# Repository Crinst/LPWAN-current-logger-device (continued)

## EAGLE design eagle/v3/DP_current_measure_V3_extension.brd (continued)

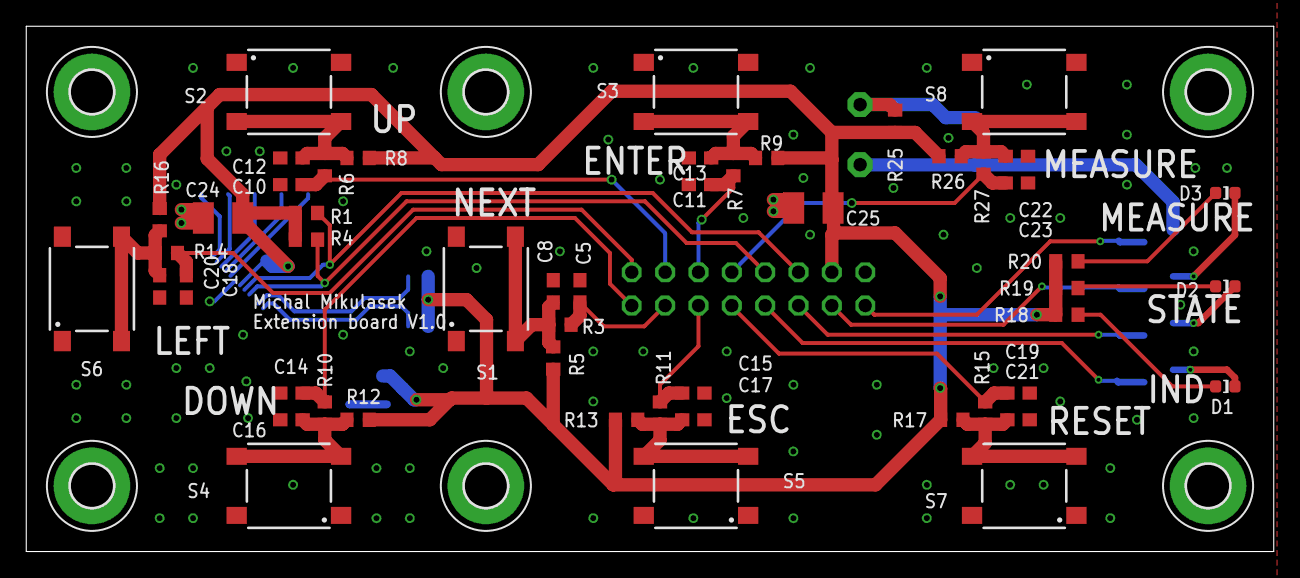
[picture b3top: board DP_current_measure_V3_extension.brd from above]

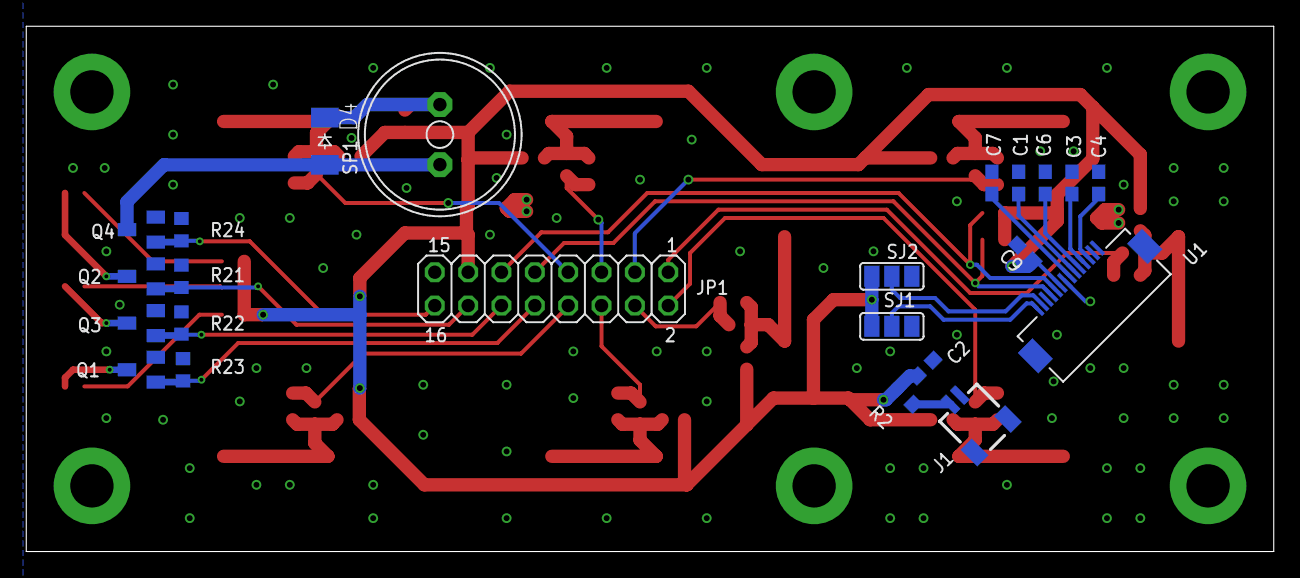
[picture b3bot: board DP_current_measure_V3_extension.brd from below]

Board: 4 copper layers, 95.0 x 40.0 mm, 80 parts (23 on the bottom side), 40 nets.

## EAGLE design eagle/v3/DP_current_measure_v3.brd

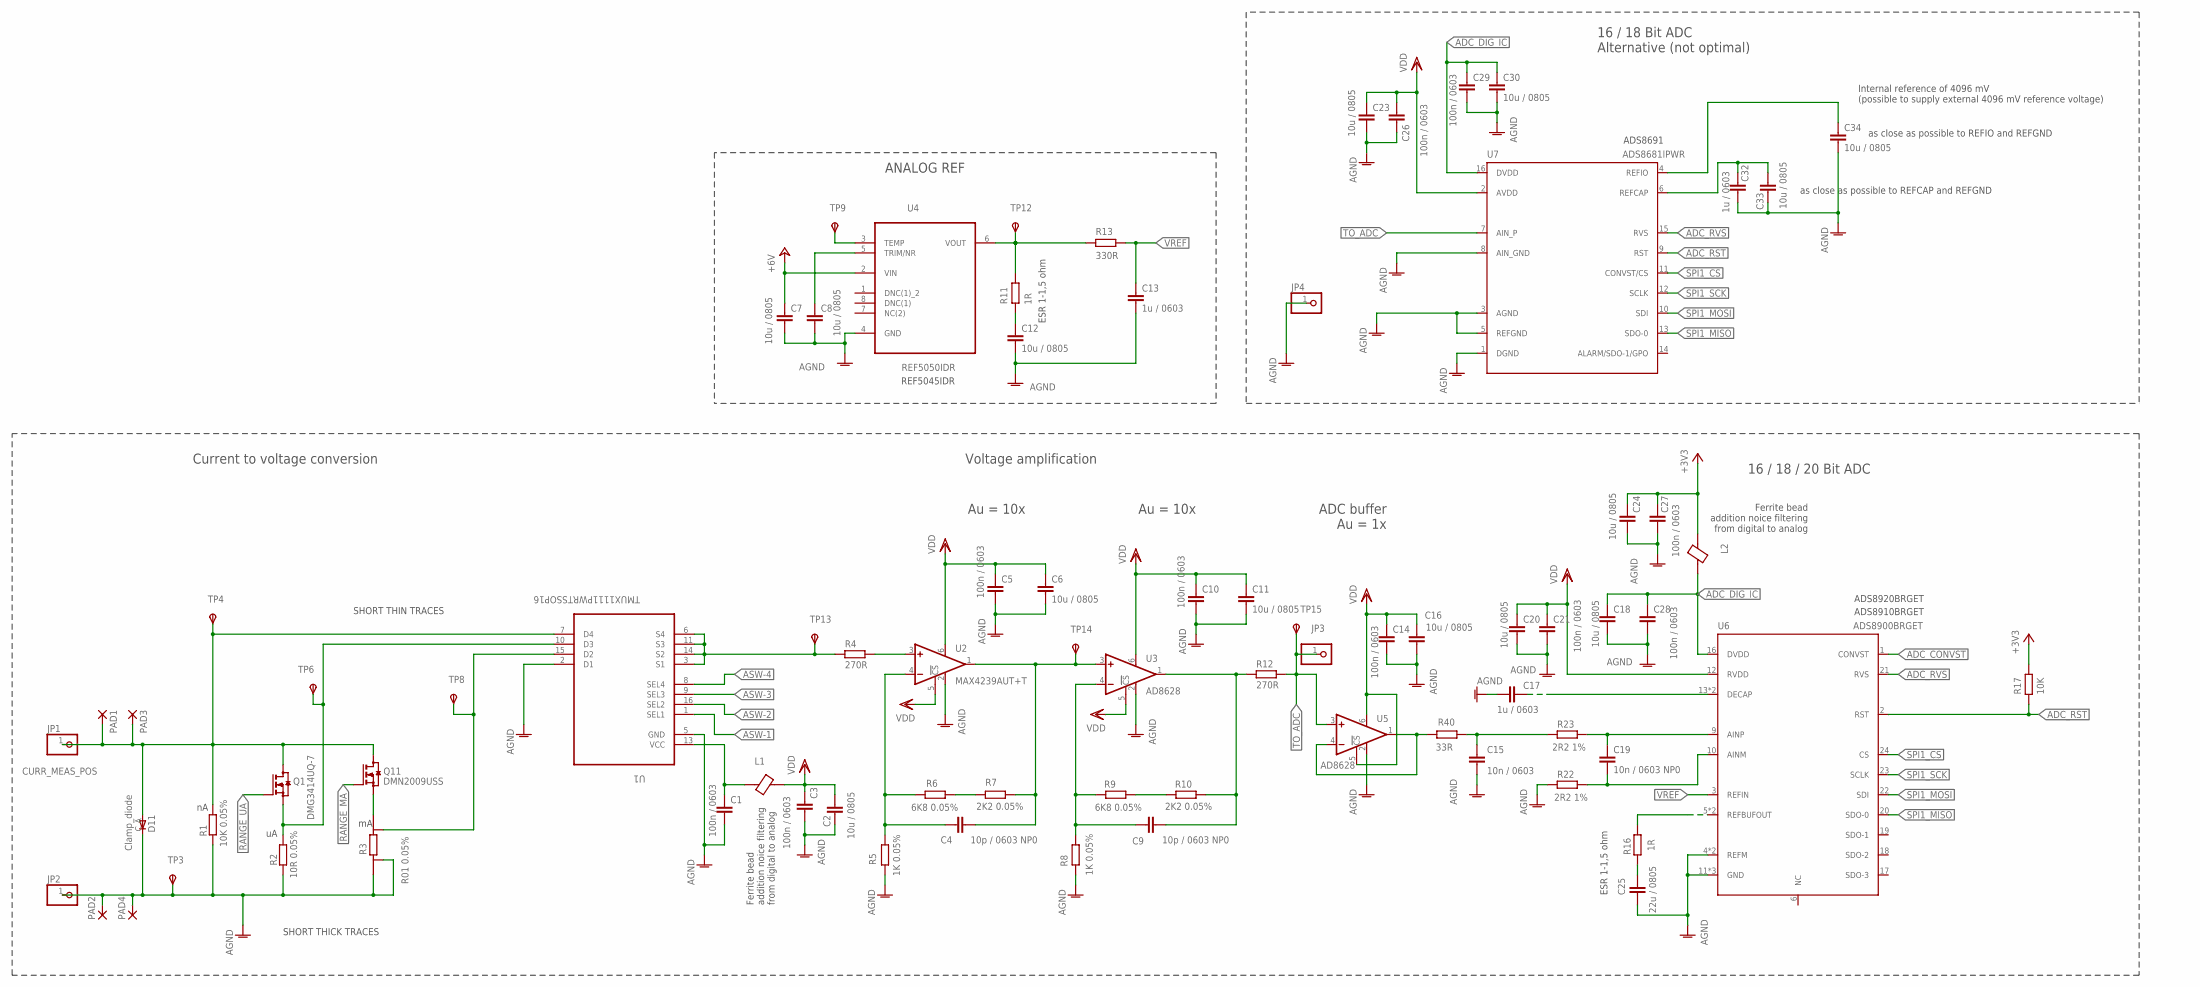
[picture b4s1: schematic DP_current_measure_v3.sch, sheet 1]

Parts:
C1, C3, C5, C10, C14, C21, C26, C27, C28, C29: 100n / 0603; C0603
C2, C6, C7, C8, C11, C12, C16, C18, C20, C23, C24, C30, C33, C34: 10u / 0805; C0805
C4, C9: 10p / 0603 NP0; C0603
C13, C17, C32: 1u / 0603; C0603
C15: 10n / 0603; C0603
C19: 10n / 0603 NP0; C0603
C25: 22u / 0805; C0805
D11: Clamp_diode; DO214AC
JP1, JP2, JP3, JP4: PINHD-1X1; 1X01
L1, L2: BLM21PG331SN1D
PAD1, PAD2, PAD3, PAD4: WIREPADSMD2,54-5,08; SMD2,54-5,08
Q1: DMG3414UQ-7; SOT23
Q11: DMN2009USS; SO8
R1: 10K 0.05%; R0805
R2: 10R 0.05%; R0805
R3: R01 0.05%; R2512
R4, R12: 270R; R0603
R5, R8: 1K 0.05%; R0603
R6, R9: 6K8 0.05%; R0603
R7, R10: 2K2 0.05%; R0603
R11, R16: 1R; R0603
R13: 330R; R0603
R17: 10K; R0603
R22, R23: 2R2 1%; R0603
R40: 33R; R0603
TP3, TP4, TP6, TP8, TP9, TP12, TP13, TP14, TP15: TPSB1,27; B1,27
U1: TMUX1111PWRTSSOP16; SOP65P640X110-16N
U2: MAX4239AUT+T; SOT23-6
U3, U5: AD8628; SOT23-6
U4: REF5050IDR; SOIC127P600X175-8N
U6: ADS8900BRGET; 24-VFQFN
U7: ADS8681IPWR; SOP65P640X120-16N

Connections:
+3V3: C24.1, C27.1, L2.2, R17.2; also elsewhere on the board
+6V: C7.1, U4.2 (VIN); also elsewhere on the board
ADC_CONVST: U6.1 (CONVST); also elsewhere on the board
ADC_DIG_IC: C18.1, C28.1, C29.1, C30.1, L2.1, U6.16 (DVDD), U7.16 (DVDD)
ADC_RST: R17.1, U6.2 (RST), U7.9 (RST); also elsewhere on the board
ADC_RVS: U6.21 (RVS), U7.15 (RVS); also elsewhere on the board
AGND: C1.2, C2.2, C3.2, C5.2, C6.2, C7.2, C8.2, C10.2, C11.2, C12.2, C13.2, C14.2, C15.2, C16.2, C17.2, C18.2, C20.2, C21.2, C23.2, C24.2, C25.2, C26.2, C27.2, C28.2, C29.2, C30.2, C32.2, C33.2, C34.2, D11.C, JP2.1, JP4.1, PAD2.1, PAD4.1, R1.2, R2.2, R3.E1, R3.I1, R5.1, R8.2, R22.1, TP3.TP, U1.2 (D1), U1.5 (GND), U2.2 (V-), U3.2 (V-), U4.4 (GND), U5.2 (V-), U6.4 (REFM), U6.8 (REFM), U6.11 (GND), U6.15 (GND), U6.25 (GND), U7.1 (DGND), U7.3 (AGND), U7.5 (REFGND), U7.8 (AIN_GND); also elsewhere on the board
ASW-1: U1.1 (SEL1); also elsewhere on the board
ASW-2: U1.16 (SEL2); also elsewhere on the board
ASW-3: U1.9 (SEL3); also elsewhere on the board
ASW-4: U1.8 (SEL4); also elsewhere on the board
CURR_MEAS_POS: D11.A, JP1.1, PAD1.1, PAD3.1, Q1.3 (D), Q11.5 (D), Q11.6 (D), Q11.7 (D), Q11.8 (D), R1.1, TP4.TP, U1.7 (D4)
MA_RANGE_SENSE: R3.E2, TP8.TP, U1.15 (D2)
MA_RANGE_SENSE_Q: Q11.1 (S), Q11.2 (S), Q11.3 (S), R3.I2
unnamed: C9.2, R10.1, R12.1, U3.1 (OUT)
unnamed: R9.1, R10.2
unnamed: C9.1, R8.1, R9.2, U3.4 (-IN)
unnamed: R6.2, R7.1
unnamed: C4.2, R7.2, TP14.TP, U2.1 (OUT), U3.3 (+IN)
unnamed: R4.1, TP13.TP, U1.3 (S1), U1.6 (S4), U1.11 (S3), U1.14 (S2)
unnamed: C4.1, R5.2, R6.1, U2.4 (-IN)
unnamed: C1.1, L1.1, U1.13 (VCC)
unnamed: C15.1, R23.1, R40.2
unnamed: R4.2, U2.3 (+IN)
unnamed: C19.2, R22.2, U6.10 (AINM)
unnamed: C8.1, U4.5 (TRIM/NR)
unnamed: C32.1, C33.1, U7.6 (REFCAP)
unnamed: C34.1, U7.4 (REFIO)
unnamed: TP9.TP, U4.3 (TEMP)
unnamed: R16.2, U6.5 (REFBUFOUT), U6.7 (REFBUFOUT)
unnamed: C25.1, R16.1
unnamed: C17.1, U6.13 (DECAP), U6.14 (DECAP)
unnamed: R40.1, U5.1 (OUT), U5.4 (-IN)
unnamed: C12.1, R11.2
unnamed: C19.1, R23.2, U6.9 (AINP)
RANGE_MA: Q11.4 (G); also elsewhere on the board
RANGE_UA: Q1.1 (G); also elsewhere on the board
SPI1_CS: U6.24 (CS), U7.11 (CONVST/CS); also elsewhere on the board
SPI1_MISO: U6.20 (SDO-0), U7.13 (SDO-0); also elsewhere on the board
SPI1_MOSI: U6.22 (SDI), U7.10 (SDI); also elsewhere on the board
SPI1_SCK: U6.23 (SCLK), U7.12 (SCLK); also elsewhere on the board
TO_ADC: JP3.1, R12.2, TP15.TP, U5.3 (+IN), U7.7 (AIN_P)
UA_RANGE_SENSE: Q1.2 (S), R2.1, TP6.TP, U1.10 (D3)
VDD: C2.1, C3.1, C5.1, C6.1, C10.1, C11.1, C14.1, C16.1, C20.1, C21.1, C23.1, C26.1, L1.2, U2.5 (!CS), U2.6 (V+), U3.5 (!CS), U3.6 (V+), U5.5 (!CS), U5.6 (V+), U6.12 (RVDD), U7.2 (AVDD); also elsewhere on the board
VREF: C13.1, R13.2, U6.3 (REFIN)
VREF_IC: R11.1, R13.1, TP12.TP, U4.6 (VOUT)

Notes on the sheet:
SHORT THICK TRACES
SHORT THIN TRACES
as close as possible to REFIO and REFGND
as close as possible to REFCAP and REFGND
ADS8691
REF5045IDR
16 / 18 Bit ADC Alternative (not optimal)
Internal reference of 4096 mV (possible to supply external 4096 mV reference voltage)
ANALOG REF
ESR 1-1,5 ohm
Ferrite bead addition noice filtering from digital to analog
Current to voltage conversion
16 / 18 / 20 Bit ADC
ADS8920BRGET
ADS8910BRGET
ADC buffer Au = 1x
Au = 10x
Voltage amplification

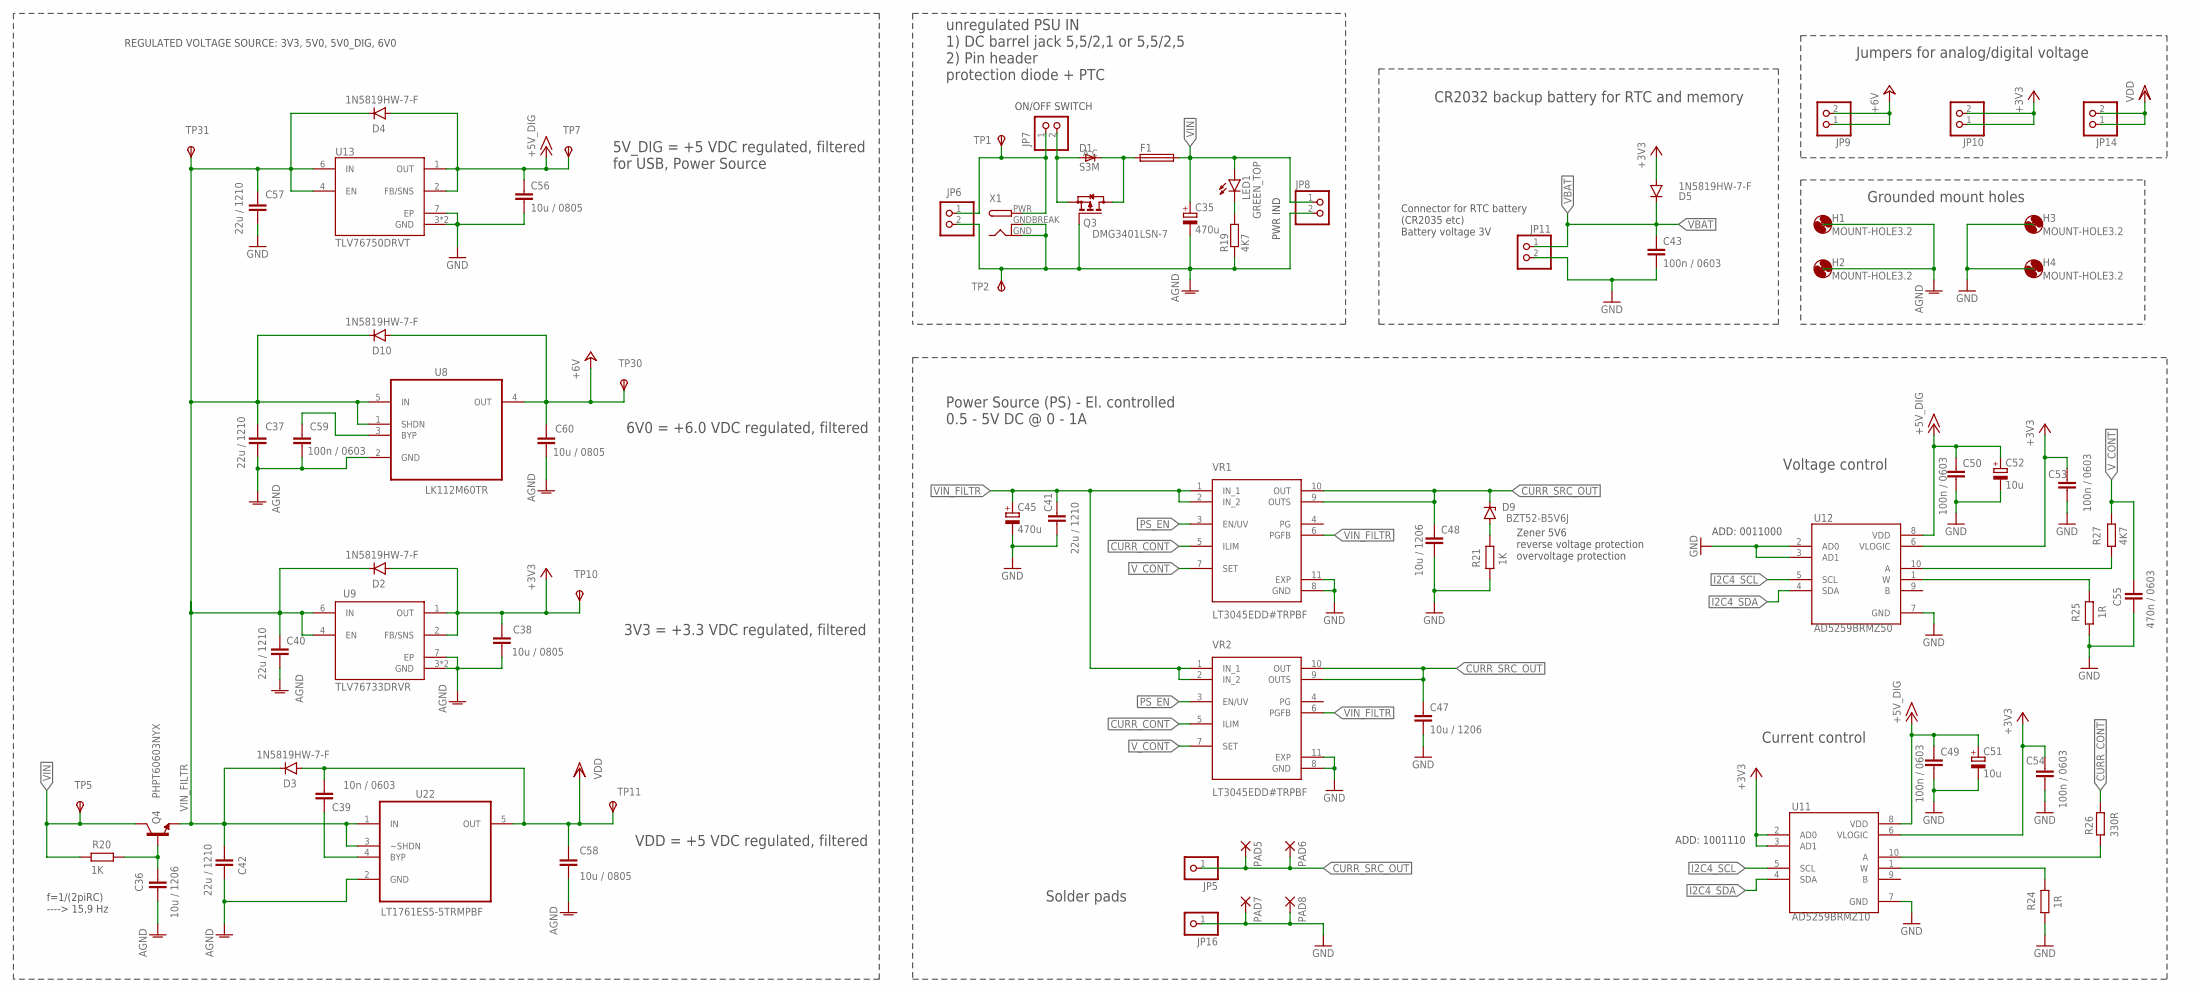
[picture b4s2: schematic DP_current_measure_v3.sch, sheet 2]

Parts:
C35, C45: 470u; PANASONIC_G
C36, C47, C48: 10u / 1206; C1206
C37, C40, C41, C42, C57: 22u / 1210; C1210
C38, C56, C58, C60: 10u / 0805; C0805
C39: 10n / 0603; C0603
C43, C49, C50, C53, C54, C59: 100n / 0603; C0603
C51, C52: 10u; SMC_B
C55: 470n / 0603; C0603
D1: S3M; DO214AC
D2, D3, D4, D5, D10: 1N5819HW-7-F; SOD-123_MINI-SMA
D9: BZT52-B5V6J; SODFL3718X115
F1: MF-MSMF050-2; 1812
H1, H2, H3, H4: MOUNT-HOLE3.2; 3,2
JP5, JP16: PINHD-1X1; 1X01
JP6, JP7, JP8, JP9, JP10, JP11, JP14: PINHD-1X2; 1X02
LED1: GREEN_TOP; CHIP-LED0603
PAD5, PAD6, PAD7, PAD8: WIREPADSMD2,54-5,08; SMD2,54-5,08
Q3: DMG3401LSN-7; SOT23
Q4: PHPT60603NYX; TO127P600X120-5N
R19, R27: 4K7; R0603
R20, R21: 1K; R0603
R24, R25: 1R; R0603
R26: 330R; R0603
TP1, TP2, TP5, TP7, TP10, TP11, TP30, TP31: TPSB1,27; B1,27
U8: LK112M60TR; SOT23-5
U9: TLV76733DRVR; SON65P200X200X80-7N
U11: AD5259BRMZ10; SOP50P490X95-10N
U12: AD5259BRMZ50; SOP50P490X95-10N
U13: TLV76750DRVT; SON65P200X200X80-7N
U22: LT1761ES5-5TRMPBF; SOT95P280X100-5N
VR1, VR2: LT3045EDD#TRPBF; SON50P300X300X80-11N
X1: DCBARRELPTH; DCJACK_2MM_PTH

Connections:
+3V3: C38.1, C53.1, C54.1, D2.A, D5.A, JP10.1, JP10.2, TP10.TP, U9.1 (OUT), U9.2 (FB/SNS), U11.2 (AD0), U11.3 (AD1), U11.6 (VLOGIC), U12.6 (VLOGIC); also elsewhere on the board
+5V_DIG: C49.1, C50.1, C51.+, C52.+, C56.1, D4.A, TP7.TP, U11.8 (VDD), U12.8 (VDD), U13.1 (OUT), U13.2 (FB/SNS); also elsewhere on the board
+6V: C60.1, D10.A, JP9.1, JP9.2, TP30.TP, U8.4 (OUT); also elsewhere on the board
AGND: C35.-, C36.2, C37.2, C38.2, C40.2, C42.2, C58.2, C59.2, C60.2, JP6.2, JP8.2, Q3.1 (G), R19.1, TP2.TP, U8.2 (GND), U9.3 (GND), U9.5 (GND), U9.7 (EP), U22.2 (GND), X1.GND, X1.GNDBREAK; also elsewhere on the board
CURR_CONT: R26.2, VR1.5 (ILIM), VR2.5 (ILIM)
CURR_CONT_LOW: R24.2, U11.1 (W)
CURR_POT_HIGH: R26.1, U11.10 (A)
CURR_SRC_OUT: C47.1, C48.1, D9.2 (C), JP5.1, PAD5.1, PAD6.1, VR1.9 (OUTS), VR1.10 (OUT), VR2.9 (OUTS), VR2.10 (OUT)
GND: C41.2, C43.2, C45.-, C47.2, C48.2, C49.2, C50.2, C51.-, C52.-, C53.2, C54.2, C55.2, C56.2, C57.2, JP11.2, JP16.1, PAD7.1, PAD8.1, R21.1, R24.1, R25.1, U11.7 (GND), U12.2 (AD0), U12.3 (AD1), U12.7 (GND), U13.3 (GND), U13.5 (GND), U13.7 (EP), VR1.8 (GND), VR1.11 (EXP), VR2.8 (GND), VR2.11 (EXP); also elsewhere on the board
I2C4_SCL: U11.5 (SCL), U12.5 (SCL); also elsewhere on the board
I2C4_SDA: U11.4 (SDA), U12.4 (SDA); also elsewhere on the board
unnamed: D9.1 (A), R21.2
unnamed: C59.1, U8.3 (BYP)
unnamed: C36.1, Q4.4 (B), R20.2
unnamed: D1.C, F1.1, Q3.3 (D)
unnamed: D1.A, JP7.2, Q3.2 (S)
unnamed: LED1.C, R19.2
unnamed: JP6.1, JP7.1, TP1.TP, X1.PWR
PS_EN: VR1.3 (EN/UV), VR2.3 (EN/UV); also elsewhere on the board
REG_BYPAS: C39.1, U22.4 (BYP)
VBAT: C43.1, D5.C, JP11.1; also elsewhere on the board
VDD: C39.2, C58.1, D3.A, JP14.1, JP14.2, TP11.TP, U22.5 (OUT); also elsewhere on the board
VIN: C35.+, F1.2, JP8.1, LED1.A, Q4.5 (C), R20.1, TP5.TP
VIN_FILTR: C37.1, C40.1, C41.1, C42.1, C45.+, C57.1, D2.C, D3.C, D4.C, D10.C, Q4.1 (E), Q4.2 (E), Q4.3 (E), TP31.TP, U8.1 (SHDN), U8.5 (IN), U9.4 (EN), U9.6 (IN), U13.4 (EN), U13.6 (IN), U22.1 (IN), U22.3 (~SHDN), VR1.1 (IN_1), VR1.2 (IN_2), VR1.6 (PGFB), VR2.1 (IN_1), VR2.2 (IN_2), VR2.6 (PGFB)
V_CONT: C55.1, R27.2, VR1.7 (SET), VR2.7 (SET)
V_CONT_LOW: R25.2, U12.1 (W)
V_POT_HIGH: R27.1, U12.10 (A)

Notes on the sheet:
unregulated PSU IN 1) DC barrel jack 5,5/2,1 or 5,5/2,5 2) Pin header protection diode + PTC
f=1/(2piRC) ----> 15,9 Hz
VDD = +5 VDC regulated, filtered
3V3 = +3.3 VDC regulated, filtered
PWR IND
CR2032 backup battery for RTC and memory
ON/OFF SWITCH
6V0 = +6.0 VDC regulated, filtered
Grounded mount holes
Jumpers for analog/digital voltage
REGULATED VOLTAGE SOURCE: 3V3, 5V0, 5V0_DIG, 6V0
Voltage control
Current control
ADD: 0011000
ADD: 1001110
Connector for RTC battery (CR2035 etc) Battery voltage 3V
5V_DIG = +5 VDC regulated, filtered for USB, Power Source
Power Source (PS) - El. controlled 0.5 - 5V DC @ 0 - 1A
Zener 5V6 reverse voltage protection overvoltage protection
Solder pads

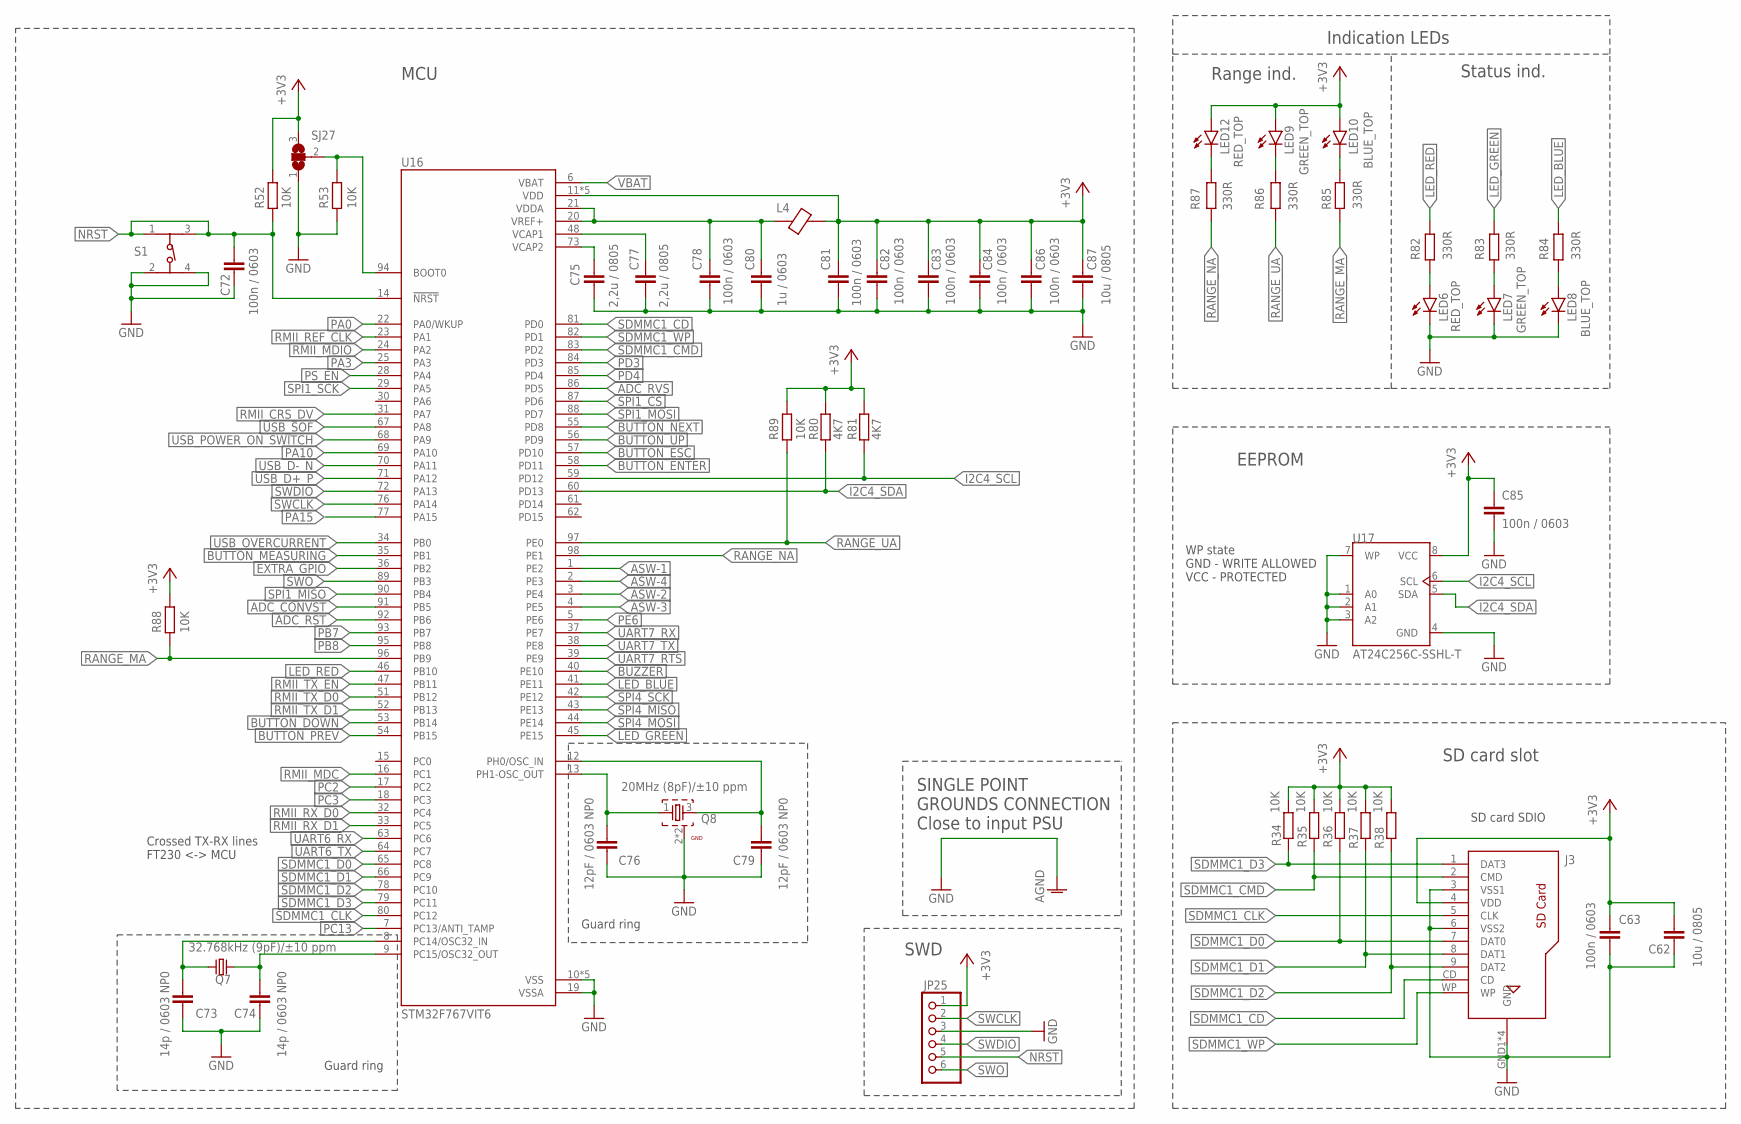
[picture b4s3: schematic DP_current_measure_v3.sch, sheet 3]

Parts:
C62, C87: 10u / 0805; C0805
C63, C72, C78, C81, C82, C83, C84, C85, C86: 100n / 0603; C0603
C73, C74: 14p / 0603 NP0; C0603
C75, C77: 2,2u / 0805; C0805
C76, C79: 12pF / 0603 NP0; C0603
C80: 1u / 0603; C0603
J3: 693063020911
JP25: PINHD-1X6; 1X06
L4: BLM21PG331SN1D
LED6, LED12: RED_TOP; CHIP-LED0603
LED7, LED9: GREEN_TOP; CHIP-LED0603
LED8, LED10: BLUE_TOP; CHIP-LED0603
Q7: 32.768kHz (9pF)/±10 ppm; WE-XTAL_IQXC-25
Q8: 20MHz (8pF)/±10 ppm; WE-XTAL_CFPX-218
R34, R35, R36, R37, R38, R52, R53, R88, R89: 10K; R0603
R80, R81: 4K7; R0603
R82, R83, R84, R85, R86, R87: 330R; R0603
S1: 430152080836
SJ27: SJ2W; SJ_2
U16: STM32F767VIT6; QFP50P1600X1600X160-100N
U17: AT24C256C-SSHL-T; SOIC127P600X175-8N

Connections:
+3V3: C62.1, C63.1, C81.1, C82.1, C83.1, C84.1, C85.1, C86.1, C87.1, J3.4 (VDD), JP25.1, L4.1, LED9.A, LED10.A, LED12.A, R34.2, R35.2, R36.2, R37.2, R38.2, R52.2, R80.2, R81.2, R88.2, R89.2, SJ27.3, U16.11 (VDD), U16.27 (VDD), U16.50 (VDD), U16.75 (VDD), U16.100 (VDD), U17.8 (VCC); also elsewhere on the board
ADC_CONVST: U16.91 (PB5); also elsewhere on the board
ADC_RST: U16.92 (PB6); also elsewhere on the board
ADC_RVS: U16.86 (PD5); also elsewhere on the board
ASW-1: U16.1 (PE2); also elsewhere on the board
ASW-2: U16.3 (PE4); also elsewhere on the board
ASW-3: U16.4 (PE5); also elsewhere on the board
ASW-4: U16.2 (PE3); also elsewhere on the board
BUTTON_DOWN: U16.53 (PB14); also elsewhere on the board
BUTTON_ENTER: U16.58 (PD11); also elsewhere on the board
BUTTON_ESC: U16.57 (PD10); also elsewhere on the board
BUTTON_MEASURING: U16.35 (PB1); also elsewhere on the board
BUTTON_NEXT: U16.55 (PD8); also elsewhere on the board
BUTTON_PREV: U16.54 (PB15); also elsewhere on the board
BUTTON_UP: U16.56 (PD9); also elsewhere on the board
BUZZER: U16.40 (PE10); also elsewhere on the board
EXTRA_GPIO: U16.36 (PB2); also elsewhere on the board
GND: C62.2, C63.2, C72.2, C73.2, C74.2, C75.2, C76.2, C77.2, C78.2, C79.2, C80.2, C81.2, C82.2, C83.2, C84.2, C85.2, C86.2, C87.2, J3.3 (VSS1), J3.6 (VSS2), J3.GND1 (GND), J3.GND2 (GND), J3.GND3 (GND), J3.GND4 (GND), JP25.3, LED6.C, LED7.C, LED8.C, Q8.2 (GND), Q8.4 (GND), R53.1, S1.2, S1.4, SJ27.1, U16.10 (VSS), U16.19 (VSSA), U16.26 (VSS), U16.49 (VSS), U16.74 (VSS), U16.99 (VSS), U17.1 (A0), U17.2 (A1), U17.3 (A2), U17.4 (GND), U17.7 (WP); also elsewhere on the board
I2C4_SCL: R81.1, U16.59 (PD12), U17.6 (SCL); also elsewhere on the board
I2C4_SDA: R80.1, U16.60 (PD13), U17.5 (SDA); also elsewhere on the board
LED_BLUE: R84.2, U16.41 (PE11); also elsewhere on the board
LED_GREEN: R83.2, U16.45 (PE15); also elsewhere on the board
LED_RED: R82.2, U16.46 (PB10); also elsewhere on the board
unnamed: C76.1, Q8.1, U16.13 (PH1-OSC_OUT)
unnamed: C79.1, Q8.3 (2), U16.12 (PH0/OSC_IN)
unnamed: C74.1, Q7.2, U16.9 (PC15/OSC32_OUT)
unnamed: C73.1, Q7.1, U16.8 (PC14/OSC32_IN)
unnamed: C75.1, U16.73 (VCAP2)
unnamed: C77.1, U16.48 (VCAP1)
unnamed: R53.2, SJ27.2, U16.94 (BOOT0)
unnamed: C78.1, C80.1, L4.2, U16.20 (VREF+), U16.21 (VDDA)
unnamed: LED8.A, R84.1
unnamed: LED7.A, R83.1
unnamed: LED6.A, R82.1
unnamed: LED12.C, R87.1
unnamed: LED9.C, R86.1
unnamed: LED10.C, R85.1
NRST: C72.1, JP25.5, R52.1, S1.1, S1.3, U16.14 (!NRST); also elsewhere on the board
PA0: U16.22 (PA0/WKUP); also elsewhere on the board
PA3: U16.25 (PA3); also elsewhere on the board
PA10: U16.69 (PA10); also elsewhere on the board
PA15: U16.77 (PA15); also elsewhere on the board
PB7: U16.93 (PB7); also elsewhere on the board
PB8: U16.95 (PB8); also elsewhere on the board
PC2: U16.17 (PC2); also elsewhere on the board
PC3: U16.18 (PC3); also elsewhere on the board
PC13: U16.7 (PC13/ANTI_TAMP); also elsewhere on the board
PD3: U16.84 (PD3); also elsewhere on the board
PD4: U16.85 (PD4); also elsewhere on the board
PE6: U16.5 (PE6); also elsewhere on the board
PS_EN: U16.28 (PA4); also elsewhere on the board
RANGE_MA: R85.2, R88.1, U16.96 (PB9); also elsewhere on the board
RANGE_NA: R87.2, U16.98 (PE1)
RANGE_UA: R86.2, R89.1, U16.97 (PE0); also elsewhere on the board
RMII_CRS_DV: U16.31 (PA7); also elsewhere on the board
RMII_MDC: U16.16 (PC1); also elsewhere on the board
RMII_MDIO: U16.24 (PA2); also elsewhere on the board
RMII_REF_CLK: U16.23 (PA1); also elsewhere on the board
RMII_RX_D0: U16.32 (PC4); also elsewhere on the board
RMII_RX_D1: U16.33 (PC5); also elsewhere on the board
RMII_TX_D0: U16.51 (PB12); also elsewhere on the board
RMII_TX_D1: U16.52 (PB13); also elsewhere on the board
RMII_TX_EN: U16.47 (PB11); also elsewhere on the board
SDMMC1_CD: J3.CD, U16.81 (PD0)
SDMMC1_CLK: J3.5 (CLK), U16.80 (PC12)
SDMMC1_CMD: J3.2 (CMD), R35.1, U16.83 (PD2)
SDMMC1_D0: J3.7 (DAT0), R36.1, U16.65 (PC8)
SDMMC1_D1: J3.8 (DAT1), R37.1, U16.66 (PC9)
SDMMC1_D2: J3.9 (DAT2), R38.1, U16.78 (PC10)
SDMMC1_D3: J3.1 (DAT3), R34.1, U16.79 (PC11)
SDMMC1_WP: J3.WP, U16.82 (PD1)
SPI1_CS: U16.87 (PD6); also elsewhere on the board
SPI1_MISO: U16.90 (PB4); also elsewhere on the board
SPI1_MOSI: U16.88 (PD7); also elsewhere on the board
SPI1_SCK: U16.29 (PA5); also elsewhere on the board
SPI4_MISO: U16.43 (PE13); also elsewhere on the board
SPI4_MOSI: U16.44 (PE14); also elsewhere on the board
SPI4_SCK: U16.42 (PE12); also elsewhere on the board
SWCLK: JP25.2, U16.76 (PA14)
SWDIO: JP25.4, U16.72 (PA13)
SWO: JP25.6, U16.89 (PB3)
UART6_RX: U16.63 (PC6); also elsewhere on the board
UART6_TX: U16.64 (PC7); also elsewhere on the board
UART7_RTS: U16.39 (PE9); also elsewhere on the board
UART7_RX: U16.37 (PE7); also elsewhere on the board
UART7_TX: U16.38 (PE8); also elsewhere on the board
USB_D+_P: U16.71 (PA12); also elsewhere on the board
USB_D-_N: U16.70 (PA11); also elsewhere on the board
USB_OVERCURRENT: U16.34 (PB0); also elsewhere on the board
USB_POWER_ON_SWITCH: U16.68 (PA9); also elsewhere on the board
USB_SOF: U16.67 (PA8)
VBAT: U16.6 (VBAT); also elsewhere on the board

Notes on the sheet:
Guard ring
WP state GND - WRITE ALLOWED VCC - PROTECTED
EEPROM
SWD
Crossed TX-RX lines FT230 <-> MCU
SD card slot
SD card SDIO
SINGLE POINT GROUNDS CONNECTION Close to input PSU
Indication LEDs
Status ind.
Range ind.
MCU

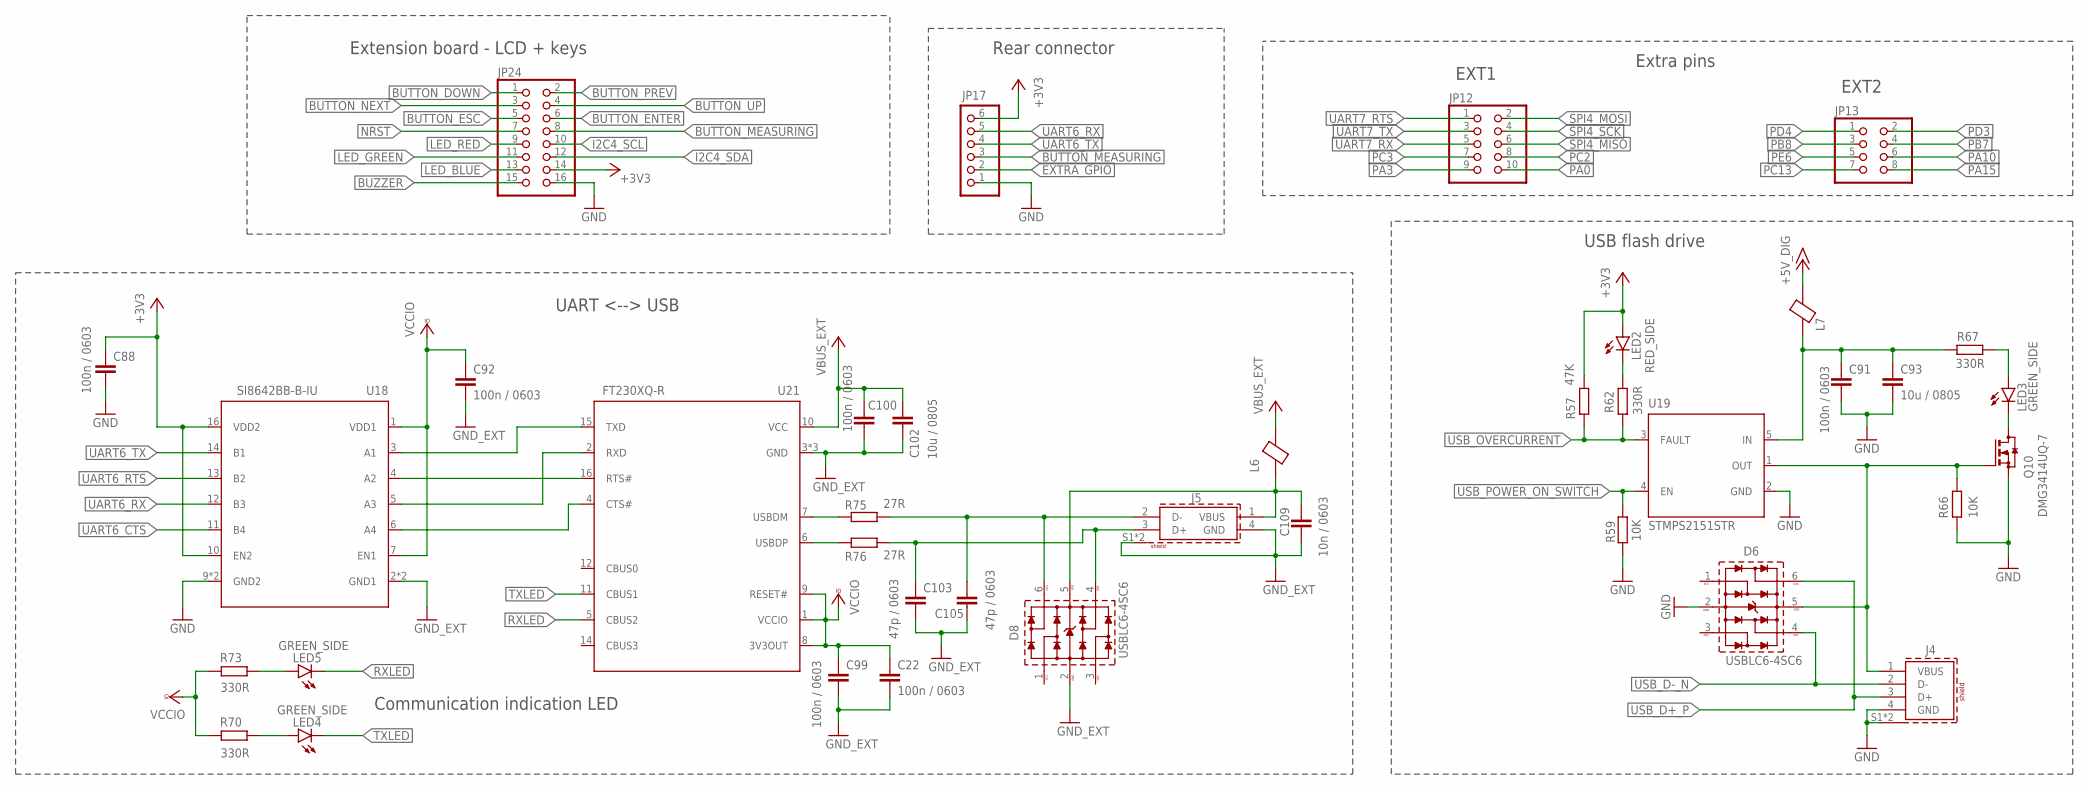
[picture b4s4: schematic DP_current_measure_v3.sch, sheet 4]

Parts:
C22, C88, C91, C92, C99, C100: 100n / 0603; C0603
C93, C102: 10u / 0805; C0805
C103, C105: 47p / 0603; C0603
C109: 10n / 0603; C0603
D6, D8: USBLC6-4SC6; WE-TVS_SOT23-6L
J4: 614004190021
J5: 61400416121
JP12: PINHD-2X5; 2X05
JP13: PINHD-2X4; 2X04
JP17: PINHD-1X6; 1X06
JP24: PINHD-2X8; 2X08
L6, L7: BLM21PG331SN1D
LED2: RED_SIDE; CHIP-LED0603
LED3, LED4, LED5: GREEN_SIDE; CHIP-LED0603
Q10: DMG3414UQ-7; SOT23
R57: 47K; R0603
R59, R66: 10K; R0603
R62, R67, R70, R73: 330R; R0603
R75, R76: 27R; R0603
U18: SI8642BB-B-IU; QSOP16
U19: STMPS2151STR; SOT-23-5
U21: FT230XQ-R; QFN16-4X4

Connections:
+3V3: C88.1, JP17.6, JP24.14, LED2.A, R57.1, U18.10 (EN2), U18.16 (VDD2); also elsewhere on the board
+5V_DIG: L7.1; also elsewhere on the board
BUTTON_DOWN: JP24.1; also elsewhere on the board
BUTTON_ENTER: JP24.6; also elsewhere on the board
BUTTON_ESC: JP24.5; also elsewhere on the board
BUTTON_MEASURING: JP17.3, JP24.8; also elsewhere on the board
BUTTON_NEXT: JP24.3; also elsewhere on the board
BUTTON_PREV: JP24.2; also elsewhere on the board
BUTTON_UP: JP24.4; also elsewhere on the board
BUZZER: JP24.15; also elsewhere on the board
CTS: U18.6 (A4), U21.4 (CTS#)
EXTRA_GPIO: JP17.2; also elsewhere on the board
GND: C88.2, C91.2, C93.2, D6.2 (GND), J4.4 (GND), J4.S1 (SHIELD), J4.S2 (SHIELD), JP17.1, JP24.16, Q10.2 (S), R59.2, R66.2, U18.9 (GND2), U18.15 (GND2), U19.2 (GND); also elsewhere on the board
GND_EXT: C22.2, C92.2, C99.2, C100.2, C102.2, C103.2, C105.2, C109.2, D8.2 (GND), J5.4 (GND), J5.S1 (SHIELD), J5.S2 (SHIELD), U18.2 (GND1), U18.8 (GND1), U21.3 (GND), U21.13 (GND), U21.EXP (GND)
I2C4_SCL: JP24.10; also elsewhere on the board
I2C4_SDA: JP24.12; also elsewhere on the board
LED_BLUE: JP24.13; also elsewhere on the board
LED_GREEN: JP24.11; also elsewhere on the board
LED_RED: JP24.9; also elsewhere on the board
unnamed: LED4.A, R70.1
unnamed: LED5.A, R73.1
unnamed: LED3.A, R67.2
unnamed: LED3.C, Q10.3 (D)
unnamed: LED2.C, R62.1
unnamed: C91.1, C93.1, L7.2, R67.1, U19.5 (IN)
NRST: JP24.7; also elsewhere on the board
PA0: JP12.10; also elsewhere on the board
PA3: JP12.9; also elsewhere on the board
PA10: JP13.6; also elsewhere on the board
PA15: JP13.8; also elsewhere on the board
PB7: JP13.4; also elsewhere on the board
PB8: JP13.3; also elsewhere on the board
PC2: JP12.8; also elsewhere on the board
PC3: JP12.7; also elsewhere on the board
PC13: JP13.7; also elsewhere on the board
PD3: JP13.2; also elsewhere on the board
PD4: JP13.1; also elsewhere on the board
PE6: JP13.5; also elsewhere on the board
RTS: U18.4 (A2), U21.16 (RTS#)
RXD: U18.5 (A3), U21.2 (RXD)
RXLED: LED5.C, U21.5 (CBUS2)
SPI4_MISO: JP12.6; also elsewhere on the board
SPI4_MOSI: JP12.2; also elsewhere on the board
SPI4_SCK: JP12.4; also elsewhere on the board
TXD: U18.3 (A1), U21.15 (TXD)
TXLED: LED4.C, U21.11 (CBUS1)
UART6_CTS: U18.11 (B4)
UART6_RTS: U18.13 (B2)
UART6_RX: JP17.5, U18.12 (B3); also elsewhere on the board
UART6_TX: JP17.4, U18.14 (B1); also elsewhere on the board
UART7_RTS: JP12.1; also elsewhere on the board
UART7_RX: JP12.5; also elsewhere on the board
UART7_TX: JP12.3; also elsewhere on the board
USBE_N: C105.1, D8.6, J5.2 (D-), R75.2
USBE_P: C103.1, D8.4, J5.3 (D+), R76.2
USB_D+_P: D6.6, J4.3 (D+); also elsewhere on the board
USB_D-_N: D6.4, J4.2 (D-); also elsewhere on the board
USB_N: R75.1, U21.7 (USBDM)
USB_OVERCURRENT: R57.2, R62.2, U19.3 (FAULT); also elsewhere on the board
USB_P: R76.1, U21.6 (USBDP)
USB_POWER_ON_SWITCH: R59.1, U19.4 (EN); also elsewhere on the board
VBUS: C109.1, D8.5 (VDD), J5.1 (VBUS), L6.2
VBUS_EXT: C100.1, C102.1, L6.1, U21.10 (VCC)
VBUS_OUT: D6.5 (VDD), J4.1 (VBUS), Q10.1 (G), R66.1, U19.1 (OUT)
VCCIO: C22.1, C92.1, C99.1, R70.2, R73.2, U18.1 (VDD1), U18.7 (EN1), U21.1 (VCCIO), U21.8 (3V3OUT), U21.9 (RESET#)

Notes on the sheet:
UART <--> USB
USB flash drive
Extension board - LCD + keys
Rear connector
Extra pins
Communication indication LED
EXT2
EXT1
